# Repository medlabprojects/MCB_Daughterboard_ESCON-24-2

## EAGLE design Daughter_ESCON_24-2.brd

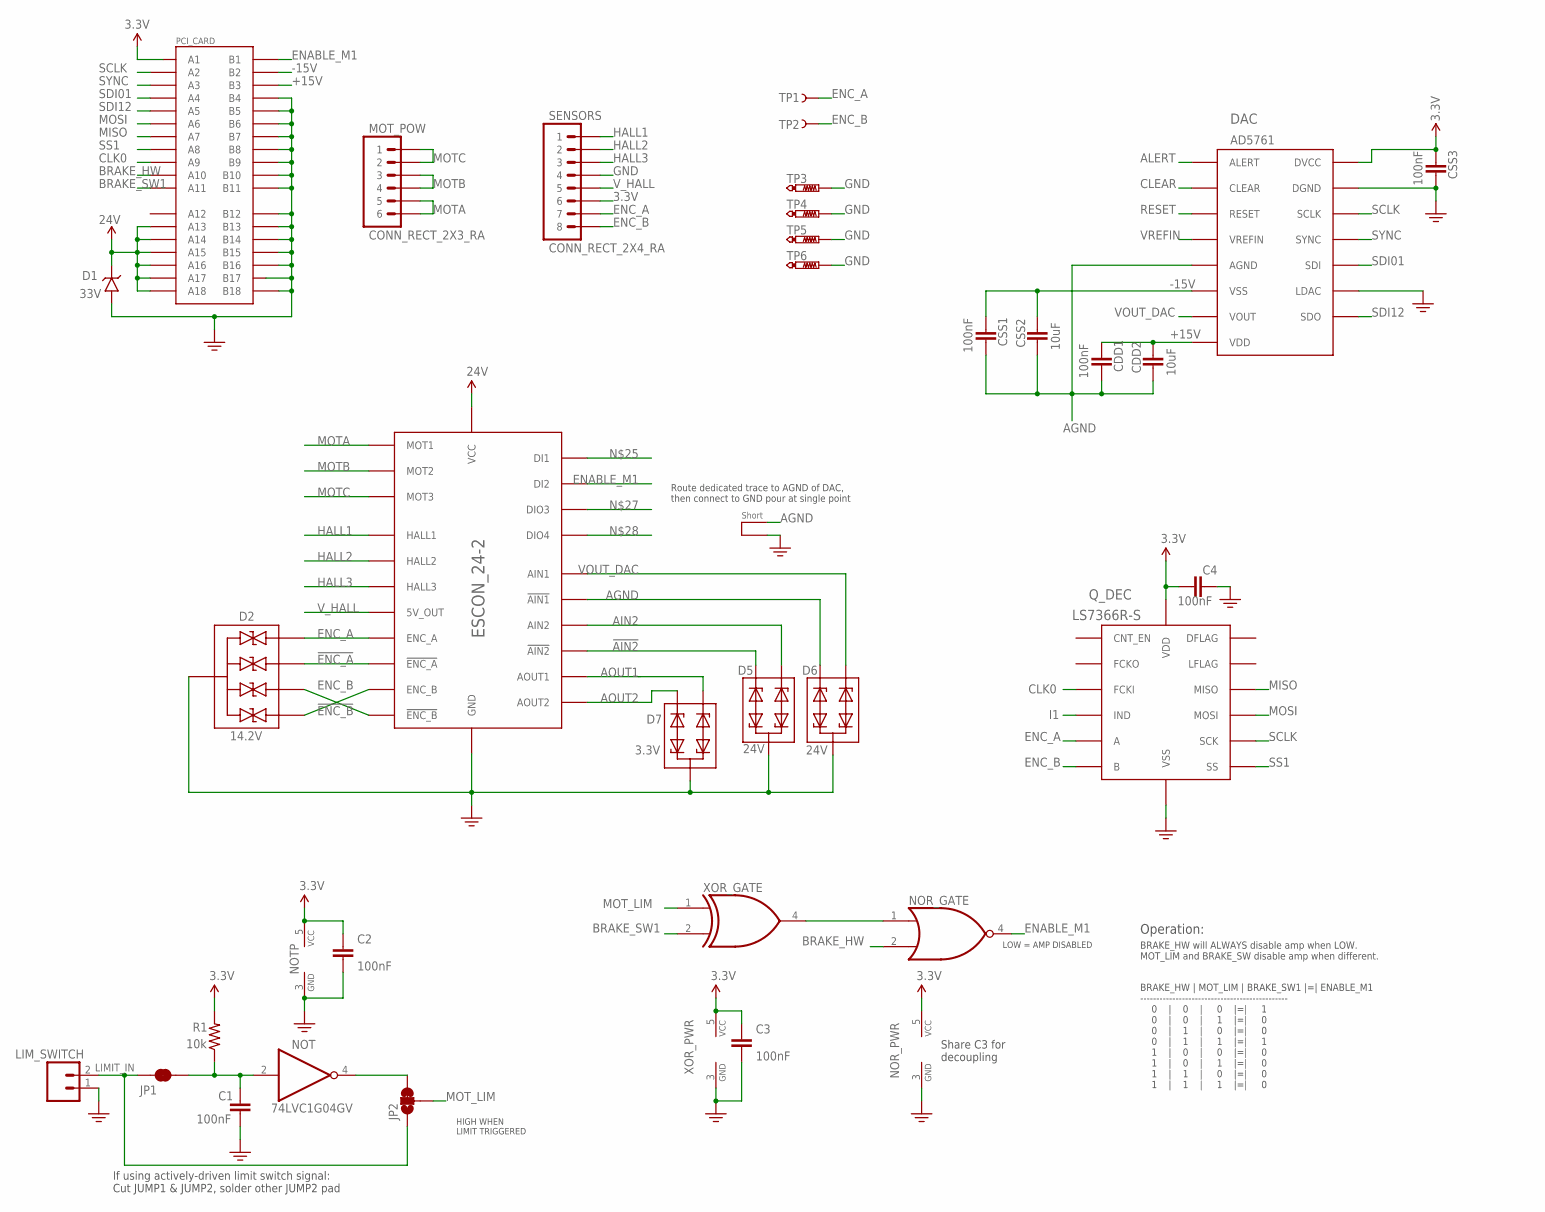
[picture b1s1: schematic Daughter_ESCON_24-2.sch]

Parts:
C1, C2, C3, C4: 100nF; 0603-CAP
CDD1: 100nF; 0603-CAP
CDD2: 10uF; C0805K
CSS1, CSS3: 100nF; 0603-CAP
CSS2: 10uF; C0805K
D1: 33V; DO214AA
D2: 14.2V; SOTFL50P160X60-6
D5, D6: 24V; SOT95P230X110-3
D7: 3.3V; SOT95P230X110-3
DAC: AD5761; TSSOP16
ESCON_24-2: ESCON_MODULE24-2_BOTTOM_ENTRY; ESCON_24-2_BOTTOM_ENTRY
JP1: JUMPER-PAD-2-NC_BY_TRACE; PAD-JUMPER-2-NC_BY_TRACE_YES_SILK
JP2: JUMPER-PAD-3-2OF3_NC_BY_TRACE; PAD-JUMPER-3-2OF3_NC_BY_TRACE_YES_SILK_FULL_BOX
LIM_SWITCH: 22-05-7028-02; 7395-02
MOT_POW: CONN_RECT_2X3_RA; 2X3-RA
NOR: NOR-SOT353; SOT353
NOT: 74LVC1G04GV; SOT23-5
PCI_CARD: PCIE-36-EDGE
Q_DEC: LS7366R-S; SOIC-14
R1: 10k; 0603-RES
SENSORS: CONN_RECT_2X4_RA; 2X4-RA
TP1, TP2: TEST-POINT_5021
TP3, TP4, TP5, TP6: PTR1TP20R; TP20R
U$1: SHORT
XOR: XOR-SOT353; SOT353

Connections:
3.3V: C2.1, C3.1, C4.1, CSS3.1, DAC.15 (DVCC), NOR.5 (VCC), NOT.5 (VCC), PCI_CARD.A1, Q_DEC.14 (VDD), R1.2, SENSORS.6, XOR.5 (VCC)
24V: D1.C, ESCON_24-2.P$4 (VCC), PCI_CARD.A13, PCI_CARD.A14, PCI_CARD.A15, PCI_CARD.A16, PCI_CARD.A17, PCI_CARD.A18
!AIN2: D5.1 (2), ESCON_24-2.P$21 (!AIN2)
!ENC_A: D2.3 (IO2), ESCON_24-2.P$11 (!ENC_A)
!ENC_B: D2.4 (IO3), ESCON_24-2.P$13 (!ENC_B)
+15V: CDD1.1, CDD2.1, DAC.8 (VDD), PCI_CARD.B3
-15V: CSS1.1, CSS2.1, DAC.6 (VSS), PCI_CARD.B2
AGND: CDD1.2, CDD2.2, CSS1.2, CSS2.2, D6.1 (2), DAC.5 (AGND), ESCON_24-2.P$23 (!AIN1), U$1.P$1
AIN2: D5.2 (1), ESCON_24-2.P$22 (AIN2)
ALERT: DAC.1 (ALERT)
AOUT1: D7.2 (1), ESCON_24-2.P$20 (AOUT1)
AOUT2: D7.1 (2), ESCON_24-2.P$19 (AOUT2)
BRAKE_HW: NOR.2 (B), PCI_CARD.A10
BRAKE_SW1: PCI_CARD.A11, XOR.2 (B)
CLEAR: DAC.2 (CLEAR)
CLK0: PCI_CARD.A9, Q_DEC.2 (FCKI)
ENABLE_M1: ESCON_24-2.P$16 (DI2), NOR.4 (Y), PCI_CARD.B1
ENC_A: D2.1 (IO1), ESCON_24-2.P$10 (ENC_A), Q_DEC.12 (A), SENSORS.7, TP1.P$1
ENC_B: D2.6 (IO4), ESCON_24-2.P$12 (ENC_B), Q_DEC.11 (B), SENSORS.8, TP2.P$1
GND: C1.2, C2.2, C3.2, C4.2, CSS3.2, D1.A, D2.2 (GND), D2.5 (GND), D5.3, D6.3, D7.3, DAC.11 (LDAC), DAC.16 (DGND), ESCON_24-2.P$5 (GND), ESCON_24-2.P$18 (GND), LIM_SWITCH.1, NOR.3 (GND), NOT.3 (GND), PCI_CARD.B4, PCI_CARD.B5, PCI_CARD.B6, PCI_CARD.B7, PCI_CARD.B8, PCI_CARD.B9, PCI_CARD.B10, PCI_CARD.B11, PCI_CARD.B12, PCI_CARD.B13, PCI_CARD.B14, PCI_CARD.B15, PCI_CARD.B16, PCI_CARD.B17, PCI_CARD.B18, Q_DEC.3 (VSS), SENSORS.4, TP3.TP, TP4.TP, TP5.TP, TP6.TP, U$1.P$2, XOR.3 (GND)
HALL1: ESCON_24-2.P$7 (HALL1), SENSORS.1
HALL2: ESCON_24-2.P$8 (HALL2), SENSORS.2
HALL3: ESCON_24-2.P$9 (HALL3), SENSORS.3
I1: Q_DEC.10 (IND)
LIMIT_IN: JP1.1, JP2.1, LIM_SWITCH.2
MISO: PCI_CARD.A7, Q_DEC.6 (MISO)
MOSI: PCI_CARD.A6, Q_DEC.7 (MOSI)
MOTA: ESCON_24-2.P$1 (MOT1), MOT_POW.5, MOT_POW.6
MOTB: ESCON_24-2.P$2 (MOT2), MOT_POW.3, MOT_POW.4
MOTC: ESCON_24-2.P$3 (MOT3), MOT_POW.1, MOT_POW.2
MOT_LIM: JP2.2, XOR.1 (A)
unnamed: C1.1, JP1.2, NOT.2 (I), R1.1
unnamed: JP2.3, NOT.4 (O)
unnamed: NOR.1 (A), XOR.4 (Y)
RESET: DAC.3 (RESET)
SCLK: DAC.14 (SCLK), PCI_CARD.A2, Q_DEC.5 (SCK)
SDI01: DAC.12 (SDI), PCI_CARD.A4
SDI12: DAC.10 (SDO), PCI_CARD.A5
SS1: PCI_CARD.A8, Q_DEC.4 (SS)
SYNC: DAC.13 (SYNC), PCI_CARD.A3
VOUT_DAC: D6.2 (1), DAC.7 (VOUT), ESCON_24-2.P$24 (AIN1)
VREFIN: DAC.4 (VREFIN)
V_HALL: ESCON_24-2.P$6 (5V_OUT), SENSORS.5

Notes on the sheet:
HIGH WHEN LIMIT TRIGGERED
LOW = AMP DISABLED
Operation:
BRAKE_HW will ALWAYS disable amp when LOW. MOT_LIM and BRAKE_SW disable amp when different.
BRAKE_HW | MOT_LIM | BRAKE_SW1 |=| ENABLE_M1 ---------------------------------------------- 0 | 0 | 0 |=| 1 0 | 0 | 1 |=| 0 0 | 1 | 0 |=| 0 0 | 1 | 1 |=| 1 1 | 0 | 0 |=| 0 1 | 0 | 1 |=| 0 1 | 1 | 0 |=| 0 1 | 1 | 1 |=| 0
If using actively-driven limit switch signal: Cut JUMP1 & JUMP2, solder other JUMP2 pad
Route dedicated trace to AGND of DAC, then connect to GND pour at single point
Share C3 for decoupling

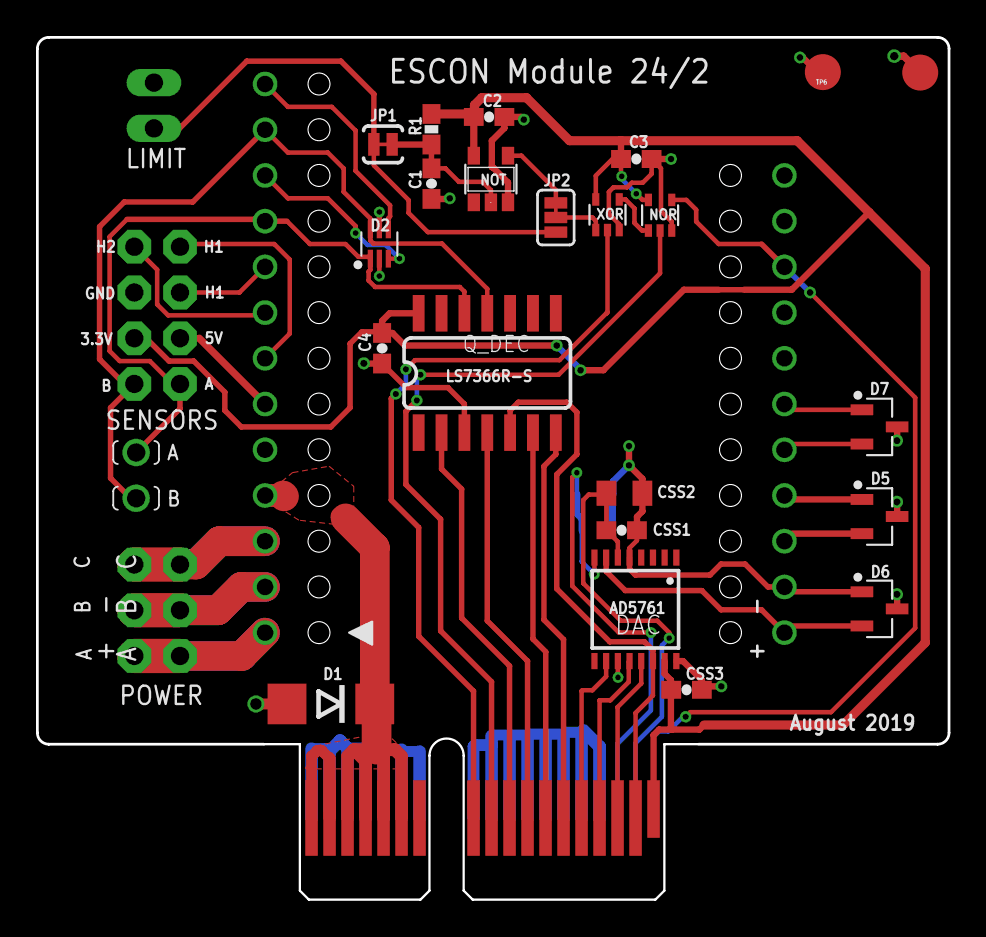
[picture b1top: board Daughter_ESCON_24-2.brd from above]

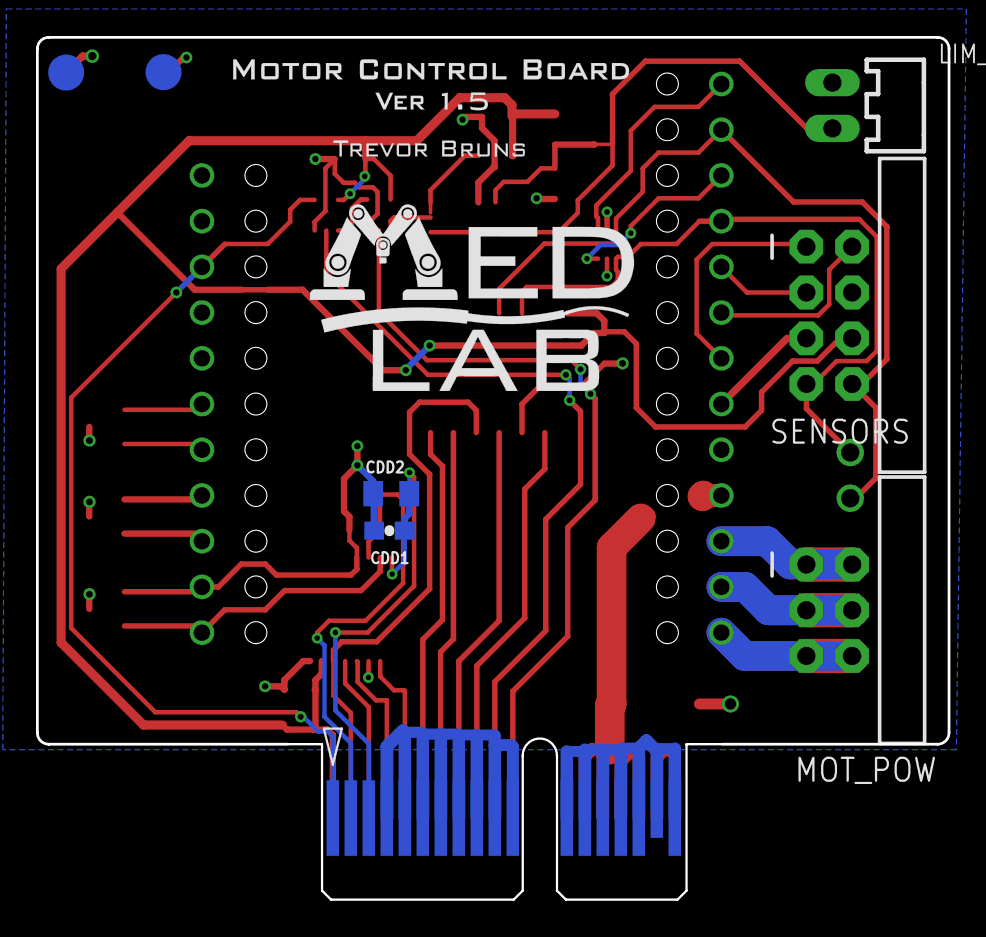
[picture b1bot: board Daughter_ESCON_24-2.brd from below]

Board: 2 copper layers, 50.6 x 47.9 mm, 36 parts (11 on the bottom side), 38 nets.

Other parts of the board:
U$3: LOGO_MEDLAB_0.7X0.4
U$4: LOGO_MOTOR_CONTROL_1.5_SMALL

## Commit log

2018-10-30 Added initial files
2018-11-01 Protection circuitry added but not routed
2018-11-04 Finished and generated gerbers
2019-08-14 Replaced 3.3V TVS with larger package

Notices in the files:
parts and their libraries:
SparkFun-Capacitors: Licensing: Creative Commons ShareAlike 4.0 International - https://creativecommons.org/licenses/by-sa/4.0
